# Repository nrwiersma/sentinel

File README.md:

<picture>
  <source media="(prefers-color-scheme: dark)" srcset="http://svg.wiersma.co.za/github/project.v2?title=sentinel&tag=presence%20detection&mode=dark">
  <source media="(prefers-color-scheme: light)" srcset="http://svg.wiersma.co.za/github/project.v2?title=sentinel&tag=presence%20detection">
  
</picture>

`Sentinal` is a presence detection device that uses a mmWave to detect occupancy. It can be used to control lights, fans, 
or other devices based on occupancy. It also include a light sensor to detect ambient light levels as well as a temperature 
and humidity sensor.

## Key Features

* Presence detection using LD2450 mmWave radar
* Ambient light detection using BH1750 light sensor
* Temperature and humidity detection using SHTC3 sensor
* RGB LED for status indication
* Native alarm integration

## Firmware

ESPHome firmware is available for the device. See the releases for the latest version. The firmware can be flashed 
using the [ESPHome Web installer](https://web.esphome.io).

## Hardware

The hardware is based on the ESP32-C3 module and the LD2450 mmWave radar module. The device is designed to be low power 
and can be powered using a 12v power supply, which is fairly common in home alarm systems.

See the [Schematic](/blob/main/hardware/schematic.pdf) for more details on the hardware design.

### BOM

See the [Interactive BOM](https://htmlpreview.github.io/?https://github.com/nrwiersma/sentinel/blob/main/bom/ibom.html) [(provided by InteractiveHtmlBom)
](https://github.com/openscopeproject/InteractiveHtmlBom).

### Update LD2450 Firmware

* Download the HLKRadarTool on your phone
* Connect to the LD2450 module via Bluetooth
* Update the firmware to version 2.04.23101915 or later

> [!WARNING]
> If upgrading the firmware version to 2.14 or later, you need to set the baud rate back to 256000 in the HLKRadarTool 
> app. This version change seems to reset the baud rate, and Sentinel will no longer be able to communicate with the LD2450 module.

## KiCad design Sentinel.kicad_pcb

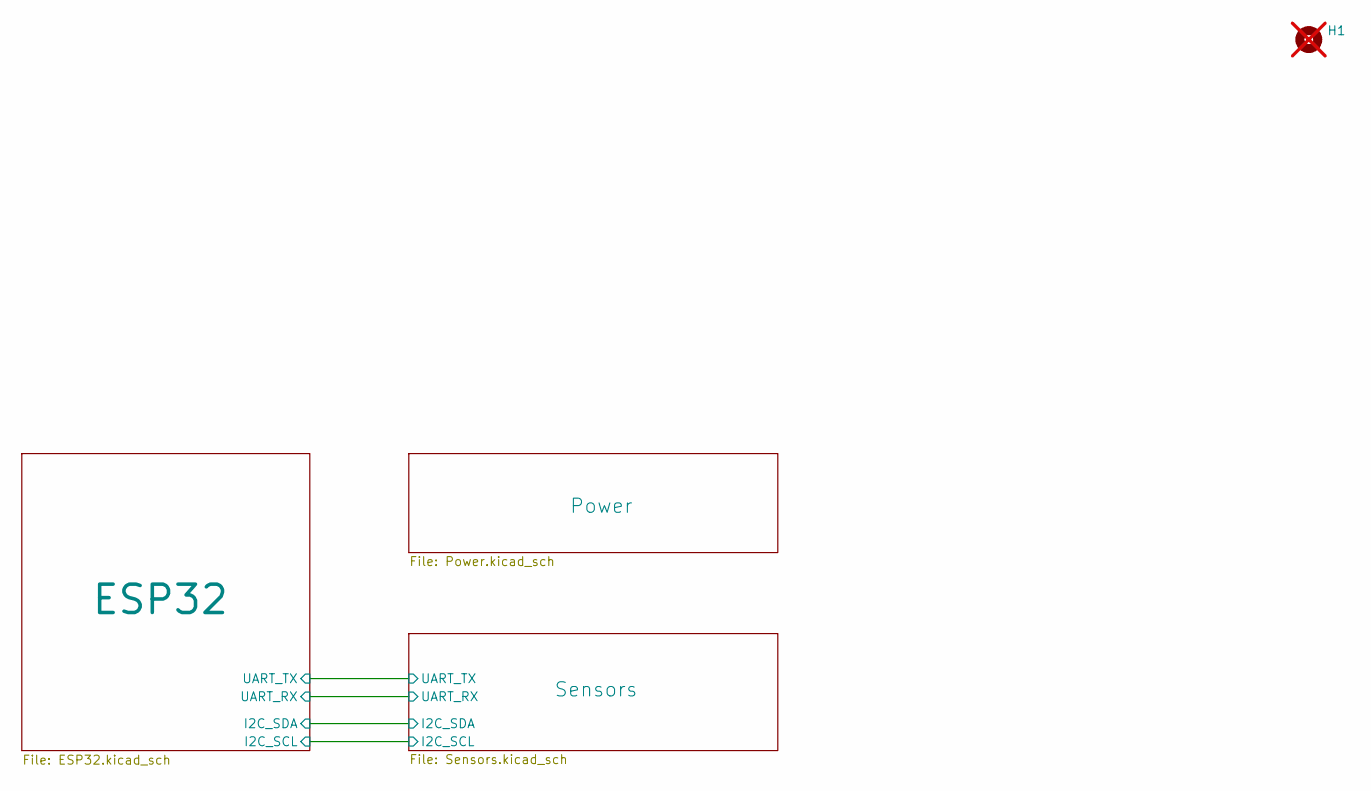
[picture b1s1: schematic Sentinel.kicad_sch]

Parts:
H1: MountingHole; MountingHole_2.2mm_M2; not fitted

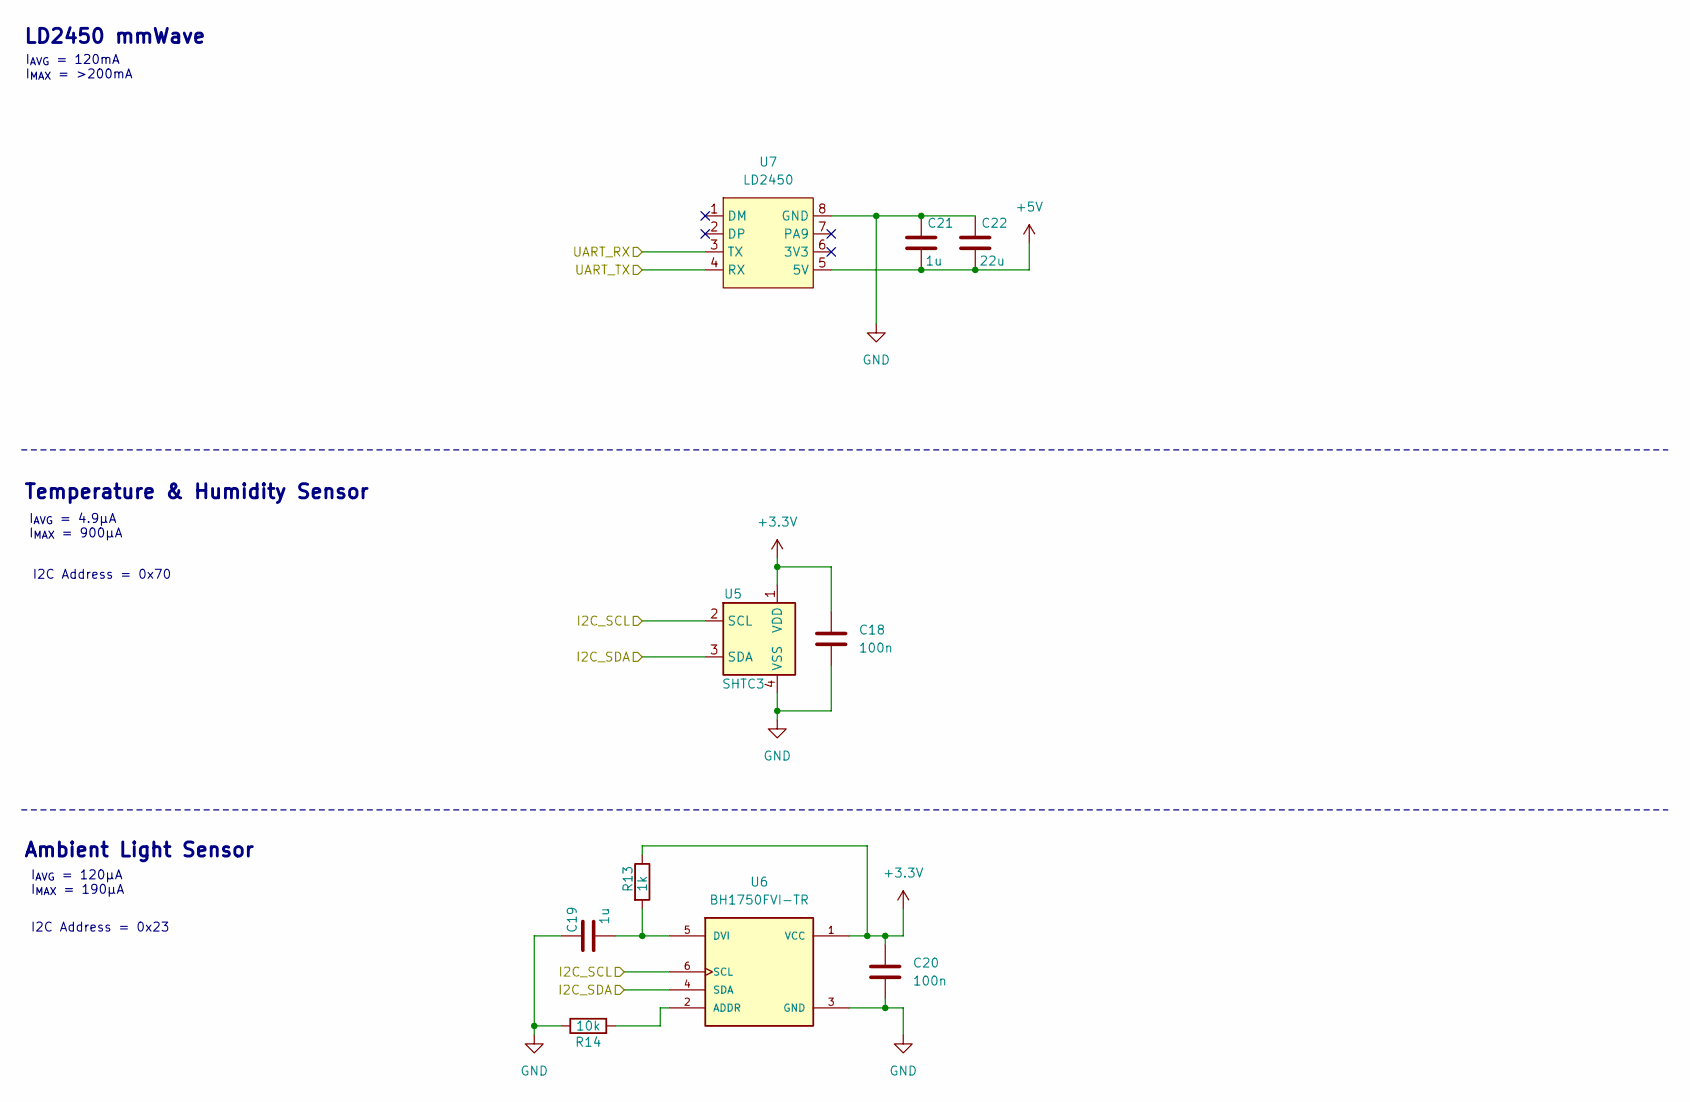
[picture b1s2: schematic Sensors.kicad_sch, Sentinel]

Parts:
C18, C20: 100n; C_0402_1005Metric; MPN CL05B104KO5NNNC; JLCPCB Part # C1525
C19, C21: 1u; C_0402_1005Metric; MPN CL05A105KP5NNNC; JLCPCB Part # C14445
C22: 22u; C_0805_2012Metric; MPN CL21A226KPCLRNC; JLCPCB Part # C318688
R13: 1k; R_0402_1005Metric; MPN RK73H1ETTP1001F; JLCPCB Part # C131360
R14: 10k; R_0402_1005Metric; MPN RC0402FR-0710KL; JLCPCB Part # C60490
U5: SHTC3; SHTC3-TR; MPN SHTC3-TR-10KS; JLCPCB Part # C2880044
U6: BH1750FVI-TR; MPN BH1750FVI-TR; JLCPCB Part # C78960
U7: LD2450; MPN 2005FV-2x4P; JLCPCB Part # C18723066

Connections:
+3.3V: C18.1, C20.1, R13.1, U5.1 (VDD), U6.1 (VCC); also elsewhere on the board
+5V: C21.2, C22.2, U7.5 (5V); also elsewhere on the board
/ESP32/I2C_SCL: U5.2 (SCL), U6.6 (SCL); also elsewhere on the board
/ESP32/I2C_SDA: U5.3 (SDA), U6.4 (SDA); also elsewhere on the board
/ESP32/UART_RX: U7.3 (TX); also elsewhere on the board
/ESP32/UART_TX: U7.4 (RX); also elsewhere on the board
GND: C18.2, C19.1, C20.2, C21.1, C22.1, R14.1, U5.4 (VSS), U6.3 (GND), U7.8 (GND); also elsewhere on the board
unnamed: R14.2, U6.2 (ADDR)
unnamed: C19.2, R13.2, U6.5 (DVI)

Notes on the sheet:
I2C Address = 0x70
I_{AVG} = 120μA I_{MAX} = 190μA
I_{AVG} = 120mA I_{MAX} = >200mA
I_{AVG} = 4.9μA I_{MAX} = 900μA
Ambient Light Sensor
LD2450 mmWave
Temperature & Humidity Sensor
I2C Address = 0x23

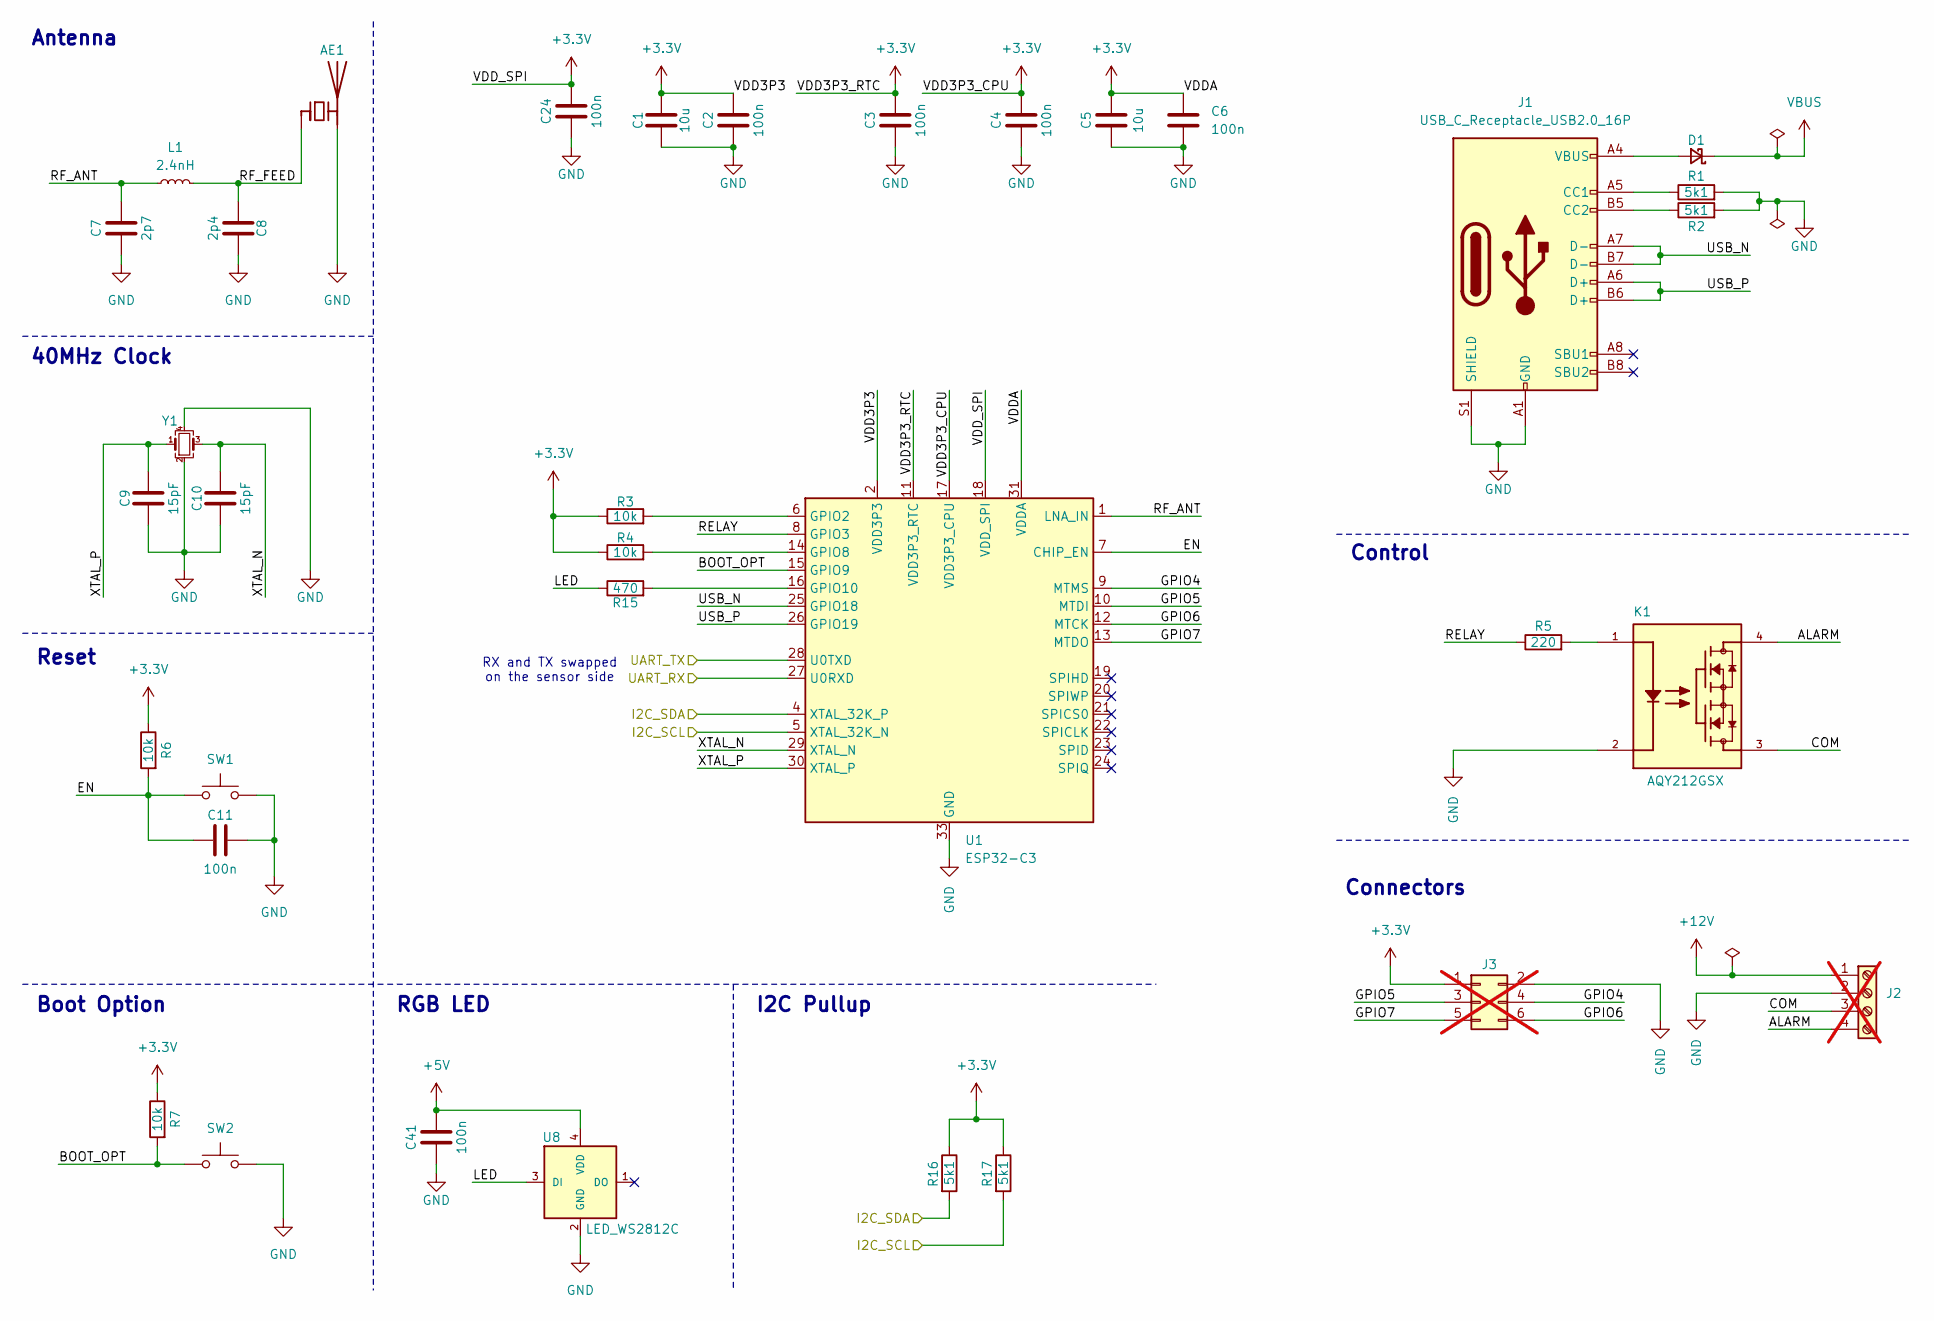
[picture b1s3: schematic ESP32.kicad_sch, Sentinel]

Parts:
AE1: Ant_RFECA3216060A1T_1206; Ant_RFECA3216060A1T; MPN RFECA3216060A1T; JLCPCB Part # C127620
C1, C5: 10u; C_0402_1005Metric; MPN CL05A106MP5NUNC; JLCPCB Part # C315248
C2, C3, C4, C6, C11, C24, C41: 100n; C_0402_1005Metric; MPN CL05B104KO5NNNC; JLCPCB Part # C1525
C7: 2p7; C_0402_1005Metric; MPN CL05C2R7BB5NNNC; JLCPCB Part # C159805
C8: 2p4; C_0402_1005Metric; MPN CL05C2R4CB5NNNC; JLCPCB Part # C318575
C9, C10: 15pF; C_0402_1005Metric; MPN CL05C150JB5NNNC; JLCPCB Part # C86285
D1: D_Schottky_Small; D_0402_1005Metric; MPN CDBQC0130L-HF; JLCPCB Part # C2886012
J1: USB_C_Receptacle_USB2.0_16P; USB_C_Receptacle_HRO_TYPE-C-31-M-12; MPN TYPE-C-31-M-12; JLCPCB Part # C165948
J2: Screw_Terminal_01x04; TerminalBlock_Phoenix_MPT-0,5-4-2.54_1x04_P2.54mm_Horizontal; not fitted
J3: Conn_02x03_Odd_Even; PinHeader_2x03_P2.54mm_Vertical; not fitted
K1: AQY212GSX; SSR_SUPSiC_GAQY212GSX; MPN GAQY212GSX; JLCPCB Part # C19271988
L1: 2.4nH; L_0402_1005Metric; MPN MLG1005S2N4BT000; JLCPCB Part # C275281
R1, R2, R16, R17: 5k1; R_0402_1005Metric; MPN RC0402FR-075K1L; JLCPCB Part # C105872
R3, R4, R6, R7: 10k; R_0402_1005Metric; MPN RC0402FR-0710KL; JLCPCB Part # C60490
R5: 220; R_0402_1005Metric; MPN RC0402FR-07220RL; JLCPCB Part # C112291
R15: 470; R_0402_1005Metric; MPN RC0402FR-7W470RL; JLCPCB Part # C606172
SW1: SW_Push; SW_Panasonic_EVQPUC; MPN EVQPUC02K; JLCPCB Part # C79174
SW2: SW_Push; SW_PTS815SJM250SMTRLFS; MPN SKRPACE010; JLCPCB Part # C139797
U1: ESP32-C3; QFN-32-1EP; MPN ESP32-C3FH4; JLCPCB Part # C2858491
U8: LED_WS2812C; LED_WS2812C-2020; MPN WS2812C-2020; JLCPCB Part # C2976072
Y1: ECS-400-10-37B2-CKM-TR; Oscillator_ECS_400-10-37B2-CKM-TR; MPN ECS-400-10-37B2-CKM-TR; JLCPCB Part # C5371760

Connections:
+3.3V: C1.1, C2.1, C3.1, C4.1, C5.1, C6.1, C24.1, J3.1, R3.1, R4.1, R6.1, R7.1, R16.1, R17.1, U1.2 (VDD3P3), U1.3 (VDD3P3), U1.11 (VDD3P3_RTC), U1.17 (VDD3P3_CPU), U1.18 (VDD_SPI), U1.31 (VDDA), U1.32 (VDDA); also elsewhere on the board
+5V: C41.1, U8.4 (VDD); also elsewhere on the board
+12V: J2.1; also elsewhere on the board
/ESP32/ALARM: J2.4, K1.4
/ESP32/BOOT_OPT: R7.2, SW2.2, U1.15 (GPIO9)
/ESP32/COM: J2.3, K1.3
/ESP32/EN: C11.1, R6.2, SW1.2, U1.7 (CHIP_EN)
/ESP32/GPIO4: J3.4, U1.9 (MTMS)
/ESP32/GPIO5: J3.3, U1.10 (MTDI)
/ESP32/GPIO6: J3.6, U1.12 (MTCK)
/ESP32/GPIO7: J3.5, U1.13 (MTDO)
/ESP32/I2C_SCL: R17.2, U1.5 (XTAL_32K_N); also elsewhere on the board
/ESP32/I2C_SDA: R16.2, U1.4 (XTAL_32K_P); also elsewhere on the board
/ESP32/LED: R15.1, U8.3 (DI)
/ESP32/RELAY: R5.1, U1.8 (GPIO3)
/ESP32/RF_ANT: C7.1, L1.1, U1.1 (LNA_IN)
/ESP32/RF_FEED: AE1.1 (FEED), C8.2, L1.2
/ESP32/UART_RX: U1.27 (U0RXD); also elsewhere on the board
/ESP32/UART_TX: U1.28 (U0TXD); also elsewhere on the board
/ESP32/USB_N: J1.A7 (D-), J1.B7 (D-), U1.25 (GPIO18)
/ESP32/USB_P: J1.A6 (D+), J1.B6 (D+), U1.26 (GPIO19)
/ESP32/XTAL_N: C10.1, U1.29 (XTAL_N), Y1.3
/ESP32/XTAL_P: C9.1, U1.30 (XTAL_P), Y1.1
GND: AE1.2 (PCB_Trace), C1.2, C2.2, C3.2, C4.2, C5.2, C6.2, C7.2, C8.1, C9.2, C10.2, C11.2, C24.2, C41.2, J1.A1 (GND), J1.A12 (GND), J1.B1 (GND), J1.B12 (GND), J1.S1 (SHIELD), J2.2, J3.2, K1.2, R1.2, R2.2, SW1.1, SW2.1, U1.33 (GND), U8.2 (GND), Y1.2, Y1.4; also elsewhere on the board
unnamed: D1.2 (A), J1.A4 (VBUS), J1.A9 (VBUS), J1.B4 (VBUS), J1.B9 (VBUS)
unnamed: J1.A5 (CC1), R1.1
unnamed: J1.B5 (CC2), R2.1
unnamed: K1.1, R5.2
unnamed: R3.2, U1.6 (GPIO2)
unnamed: R4.2, U1.14 (GPIO8)
unnamed: R15.2, U1.16 (GPIO10)
VBUS: D1.1 (K); also elsewhere on the board

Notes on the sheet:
Boot Option
RGB LED
Antenna
Connectors
I2C Pullup
RX and TX swapped on the sensor side
40MHz Clock
Control
Reset

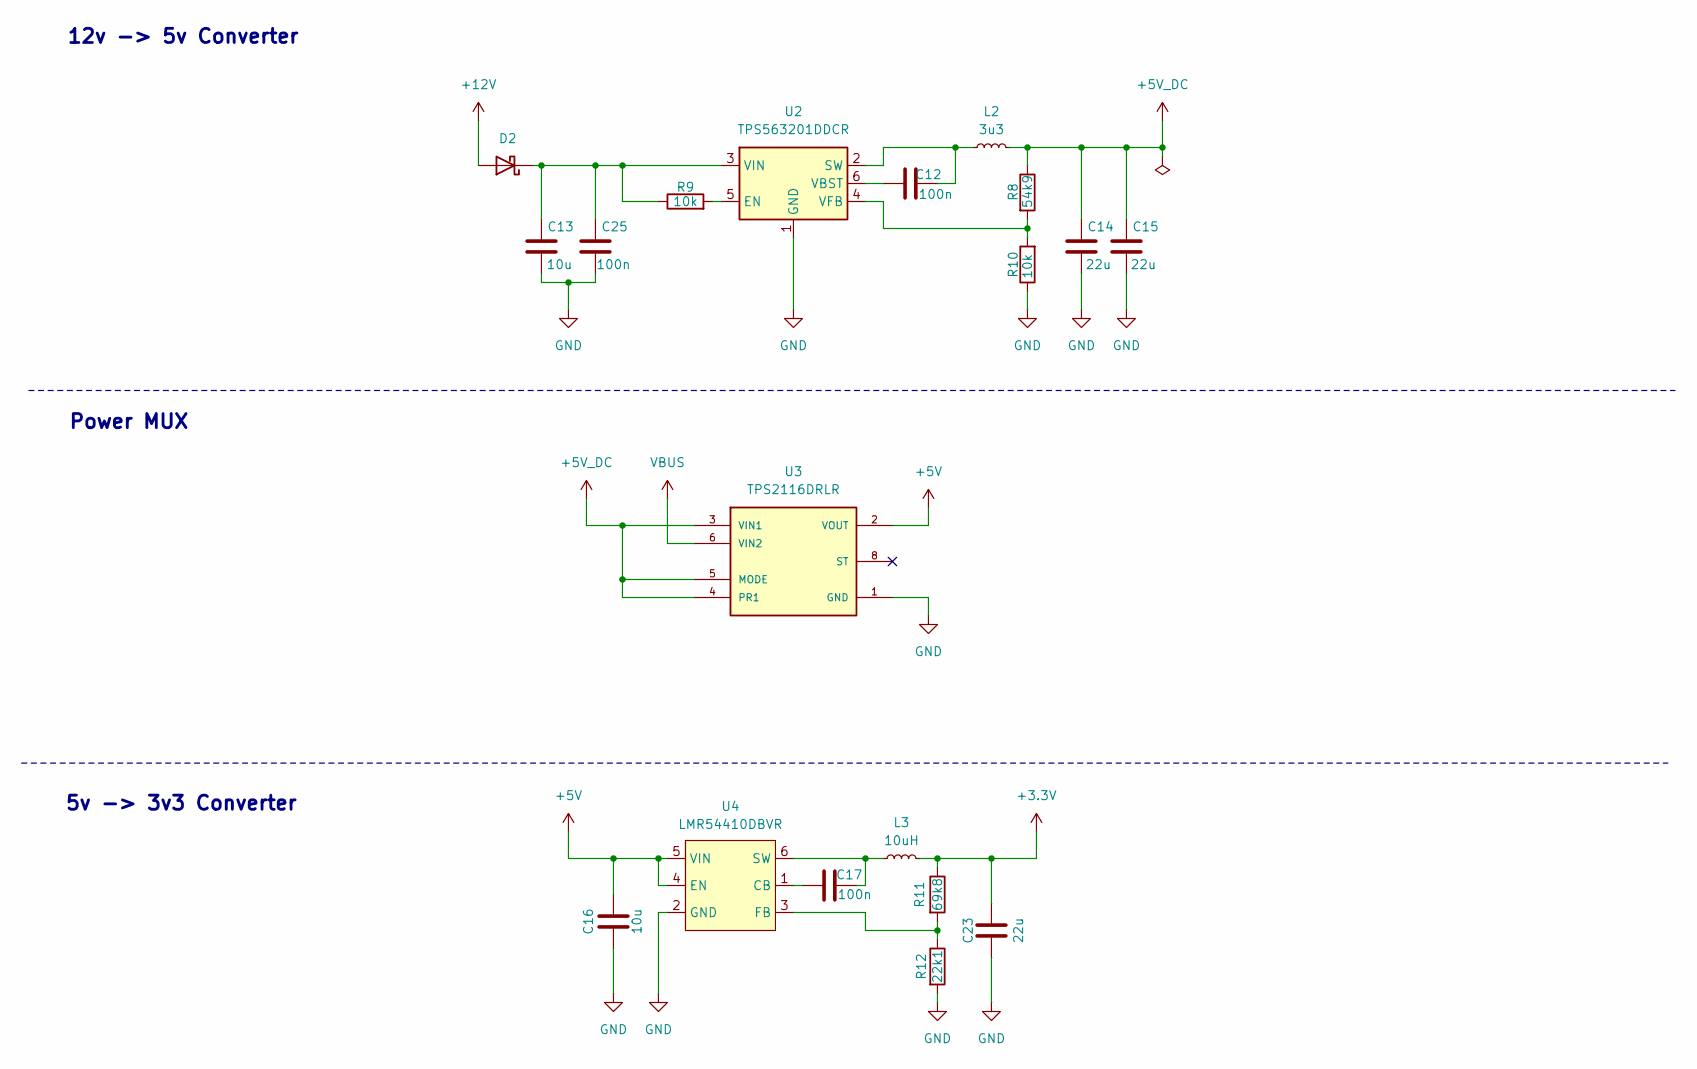
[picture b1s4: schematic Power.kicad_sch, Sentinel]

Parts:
C12, C17: 100n; C_0402_1005Metric; MPN CL05B104KO5NNNC; JLCPCB Part # C1525
C13, C16: 10u; C_0805_2012Metric; MPN CL21A106KAYNNNE; JLCPCB Part # C15850
C14, C15, C23: 22u; C_0805_2012Metric; MPN CL21A226KPCLRNC; JLCPCB Part # C318688
C25: 100n; C_0603_1608Metric; MPN CL10B104KA8NNNC; JLCPCB Part # C1590
D2: 1N5819WS; D_SOD-323; MPN 1N5819WS; JLCPCB Part # C191023
L2: 3u3; L_Chilisin_BMRx00060630; MPN MHCI06030-3R3M-S8; JLCPCB Part # C285713
L3: 10uH; L_1210_3225Metric; MPN TMS322512ALM-100MTAA; JLCPCB Part # C20244098
R8: 54k9; R_0402_1005Metric; MPN AC0402FR-0754K9L; JLCPCB Part # C227137
R9, R10: 10k; R_0402_1005Metric; MPN RC0402FR-0710KL; JLCPCB Part # C60490
R11: 69k8; R_0402_1005Metric; MPN AC0402FR-0769K8L; JLCPCB Part # C227195
R12: 22k1; R_0402_1005Metric; MPN RC0402FR-0722K1L; JLCPCB Part # C163478
U2: TPS563201DDCR; SOT-23-6; MPN TPS563201DDCR; JLCPCB Part # C116592
U3: TPS2116DRLR; SOTFL50P160X60-8N; MPN TPS2116DRLR; JLCPCB Part # C3235557
U4: LMR54410DBVR; SOT-23-6; MPN LMR54410DBVR; JLCPCB Part # C3200265

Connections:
+3.3V: C23.2, L3.2, R11.1; also elsewhere on the board
+5V: C16.2, U3.2 (VOUT), U3.7 (VOUT), U4.4 (EN), U4.5 (VIN); also elsewhere on the board
+5V_DC: C14.1, C15.1, L2.2, R8.1, U3.3 (VIN1), U3.4 (PR1), U3.5 (MODE)
+12V: D2.2 (A); also elsewhere on the board
GND: C13.2, C14.2, C15.2, C16.1, C23.1, C25.2, R10.1, R12.2, U2.1 (GND), U3.1 (GND), U4.2 (GND); also elsewhere on the board
unnamed: C13.1, C25.1, D2.1 (K), R9.1, U2.3 (VIN)
unnamed: R9.2, U2.5 (EN)
unnamed: C12.2, L2.1, U2.2 (SW)
unnamed: C12.1, U2.6 (VBST)
unnamed: R8.2, R10.2, U2.4 (VFB)
unnamed: C17.1, U4.1 (CB)
unnamed: R11.2, R12.1, U4.3 (FB)
unnamed: C17.2, L3.1, U4.6 (SW)
VBUS: U3.6 (VIN2); also elsewhere on the board

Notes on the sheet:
5v -> 3v3 Converter
Power MUX
12v -> 5v Converter

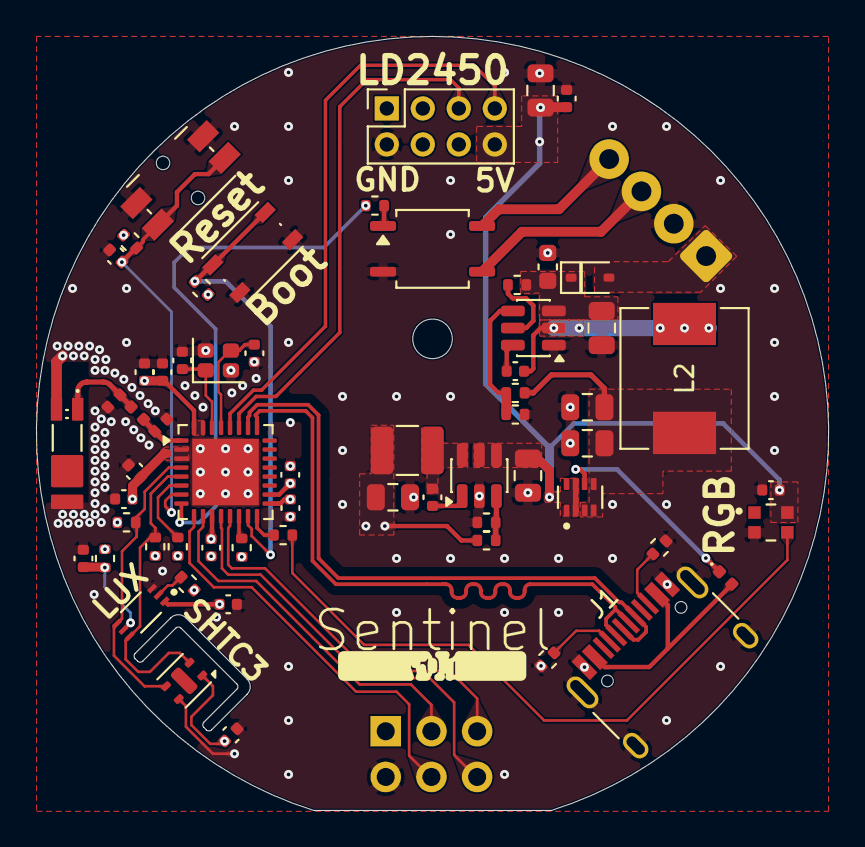
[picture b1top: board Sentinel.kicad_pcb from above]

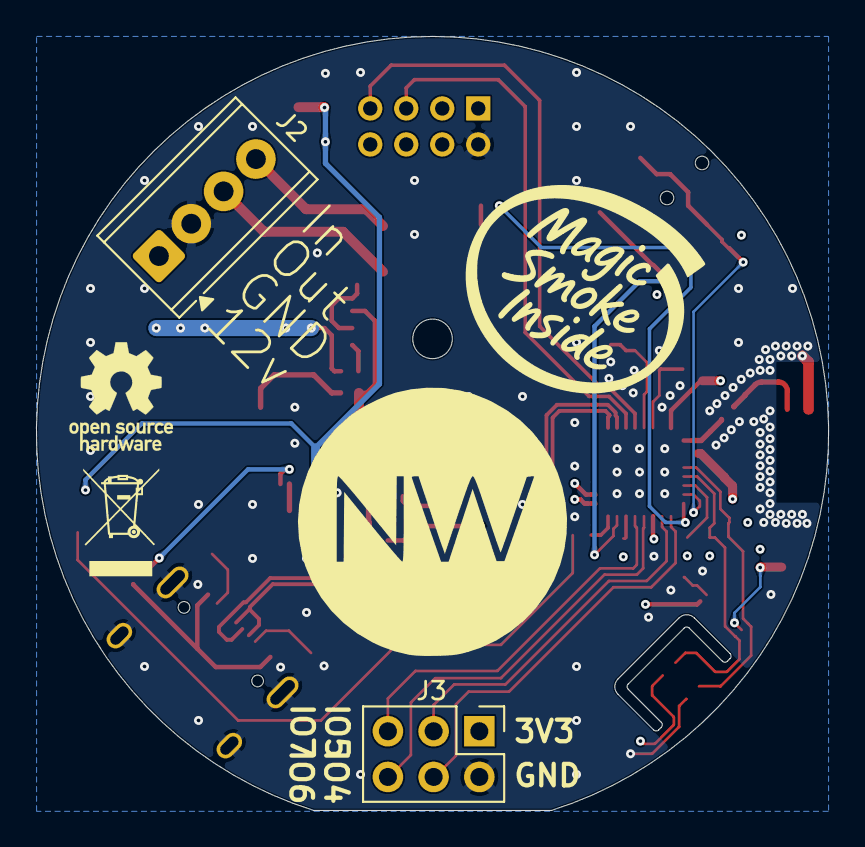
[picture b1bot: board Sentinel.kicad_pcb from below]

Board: 4 copper layers, 44.0 x 43.0 mm, 65 parts (2 on the bottom side), 43 nets.

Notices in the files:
README.md:
License: MIT
